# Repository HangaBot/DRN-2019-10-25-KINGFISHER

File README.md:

# DRN-2019-10-25-KINGFISHER
PCB Only RC QuadCopter

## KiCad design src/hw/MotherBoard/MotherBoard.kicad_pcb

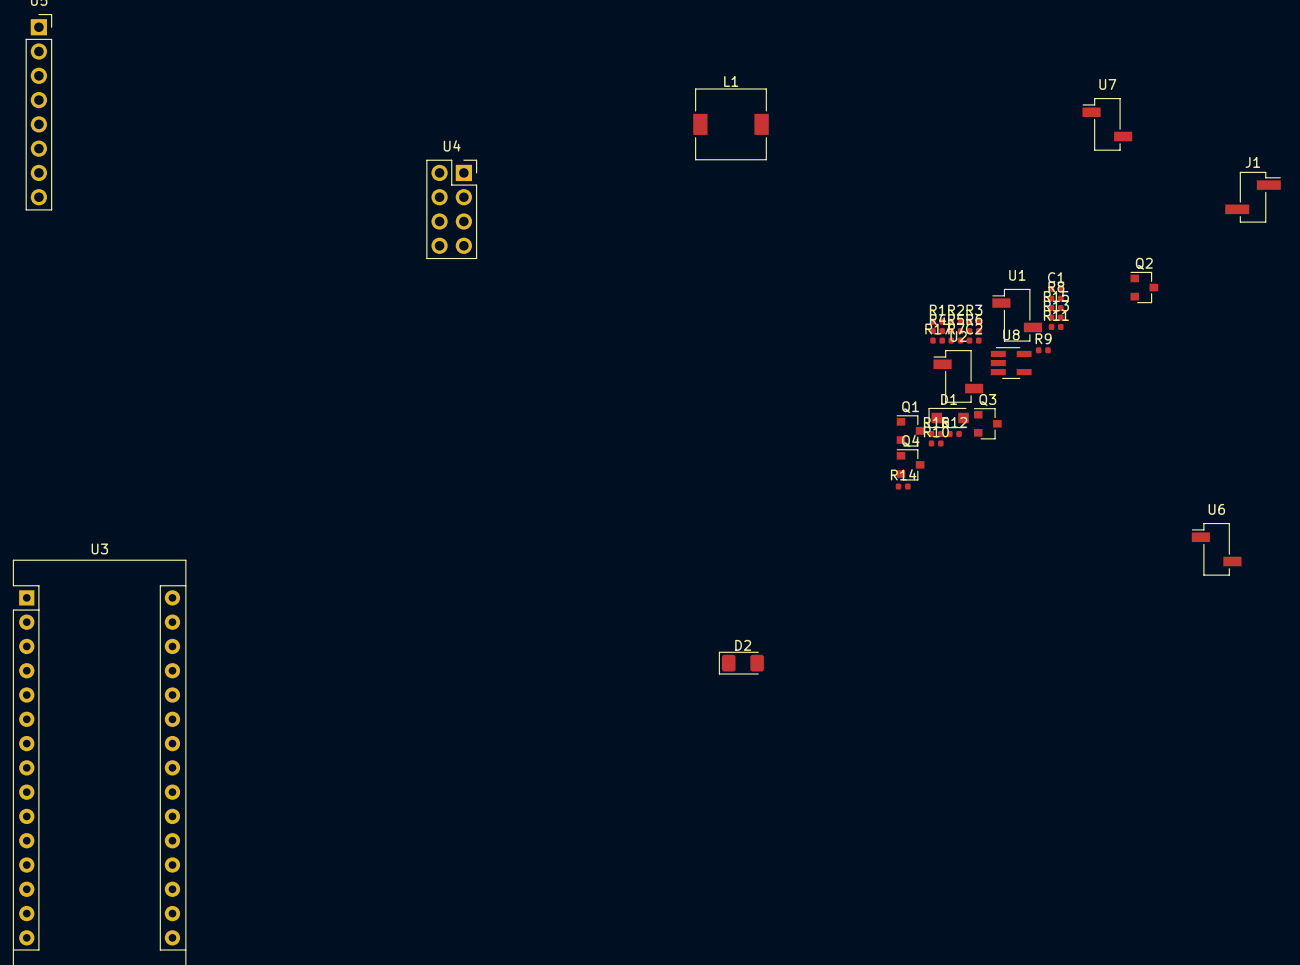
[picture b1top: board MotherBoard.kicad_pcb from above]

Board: 2 copper layers, 35 parts (0 on the bottom side), 33 nets, no tracks yet.

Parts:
C1, C2: 4u7; C_0402_1005Metric
D1: SS24FL; D_SOD-123F
D2: LED; LED_1206_3216Metric_Pad1.42x1.75mm_HandSolder
J1: Conn_01x02; PinHeader_1x02_P2.54mm_Vertical_SMD_Pin1Right
L1: 15u; L_7.3x7.3_H4.5
Q1, Q2, Q3, Q4: SQ2310ES; SOT-23
R1, R2, R12, R13: 100k; R_0402_1005Metric
R3, R4, R10, R11: 100R; R_0402_1005Metric
R5, R6, R7, R8, R9: 22R; R_0402_1005Metric
R14: 51k; R_0402_1005Metric
R15: 10k; R_0402_1005Metric
R16: 39k; R_0402_1005Metric
R17: 680; R_0402_1005Metric
U1, U2, U6, U7: 8520CorelessMotor; PinSocket_1x02_P2.54mm_Vertical_SMD_Pin1Left
U3: ArduinoNanoHeader; Arduino_Nano
U4: nRF24L01_socket; PinSocket_2x04_P2.54mm_Vertical
U5: MPU-6050-socket; PinSocket_1x08_P2.54mm_Vertical
U8: LMR64010; SOT-23-5_HandSoldering

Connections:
+3V3: U3.17, U4.2, U5.1
+6V: C2.1, D1.1, R16.1, R17.1, U3.30
+BATT: C1.1, J1.1, L1.1, R14.2, U1.1, U2.1, U6.1, U7.1, U8.5
/CE: R5.2, U3.10
/CSN: R8.1, U3.11
/MISO: R7.1, U3.15
/MOSI: R9.1, U3.14
/SCK: R6.2, U3.16
GND: C1.2, C2.2, D2.1, J1.2, Q1.2, Q2.2, Q3.2, Q4.2, R1.2, R2.2, R12.2, R13.2, R15.1, U3.4, U3.29, U4.1, U5.2, U8.2
unnamed: D1.2, L1.2, U8.1
unnamed: D2.2, R17.2
unnamed: Q1.1, R1.1, R4.2
unnamed: Q1.3, U1.2
unnamed: Q2.1, R2.1, R3.2
unnamed: Q2.3, U2.2
unnamed: Q3.1, R10.1, R12.1
unnamed: Q3.3, U6.2
unnamed: Q4.1, R11.1, R13.1
unnamed: Q4.3, U7.2
unnamed: R3.1, U3.8
unnamed: R4.1, U3.6
unnamed: R5.1, U4.3
unnamed: R6.1, U4.5
unnamed: R7.2, U4.7
unnamed: R8.2, U4.4
unnamed: R9.2, U4.6
unnamed: R10.2, U3.12
unnamed: R11.2, U3.9
unnamed: R14.1, U8.4
unnamed: R15.2, R16.2, U8.3
unnamed: U3.5, U5.8
unnamed: U3.23, U5.4
unnamed: U3.24, U5.3

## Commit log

2019-10-29 aggiunto assembly
2019-10-31 add mother board
2019-11-08 aggiunto DCDC per alimentare arduino
2019-11-08 aggiornato lo schema e la pcb della mother board
2019-11-15 aggiungi il file di outline della mother board
